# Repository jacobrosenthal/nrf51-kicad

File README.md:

Nordic provides reference designs for Altium only:
https://www.nordicsemi.com/eng/nordic/download_resource/20348/9/5180704

This is the qfac-dcdc from 2.4

Ideally you could use altium's free www.circuitmaker.com to view the paid Circuit Designer files, but thats not the case unless they have already previously been exported as an autocad file:
https://www.youtube.com/watch?v=YAWBsShCId4

As thats not the case for these Nordic files I decided to play.

In the end I finally found a 'free' viewer (for 6 months) from Altium that is really all you need to get a look at the design decisions.
http://www.altium.com/altium-designer-viewer 

However I wanted to play with kicad and https://github.com/thesourcerer8/altium2kicad to see how close it gets

Fixed issues:
* Schematic wouldnt come over for some reason, I had to build that by hand.
* The Polygons didn't come in quite right, I made them Thermal Releif's and Polygons and that seemed to help.
* I dont think you can bring in bare pads, so the antenna pad was lost on import and its signal trace was downsized. 
* Keepout Polys were lost and recreated by hand
* Stiching Vias are.. problematic, in kicad so those needed to be handled by hand https://forum.kicad.info/t/protip-nicer-via-stitching/1103/32
* via drill conversion was wierd, though Im not familar enough with kicad right now to know if it mattered, I hand edited all those a bunch
* File-Archive Footprints->Create library Exported the footprints out of the design into a proper library, and moved the .3dshapes locally as well

Known issues:
* Keepouts are really picky in kicad and Im so far too lazy to stich around all the pads, so traces in that region are showing as airwires even though theyre connected
* Altium has the no poly islands smaller than xsq but kicad doesnt appear to which means a few little islands exist on our gerbers that dont on theirs.

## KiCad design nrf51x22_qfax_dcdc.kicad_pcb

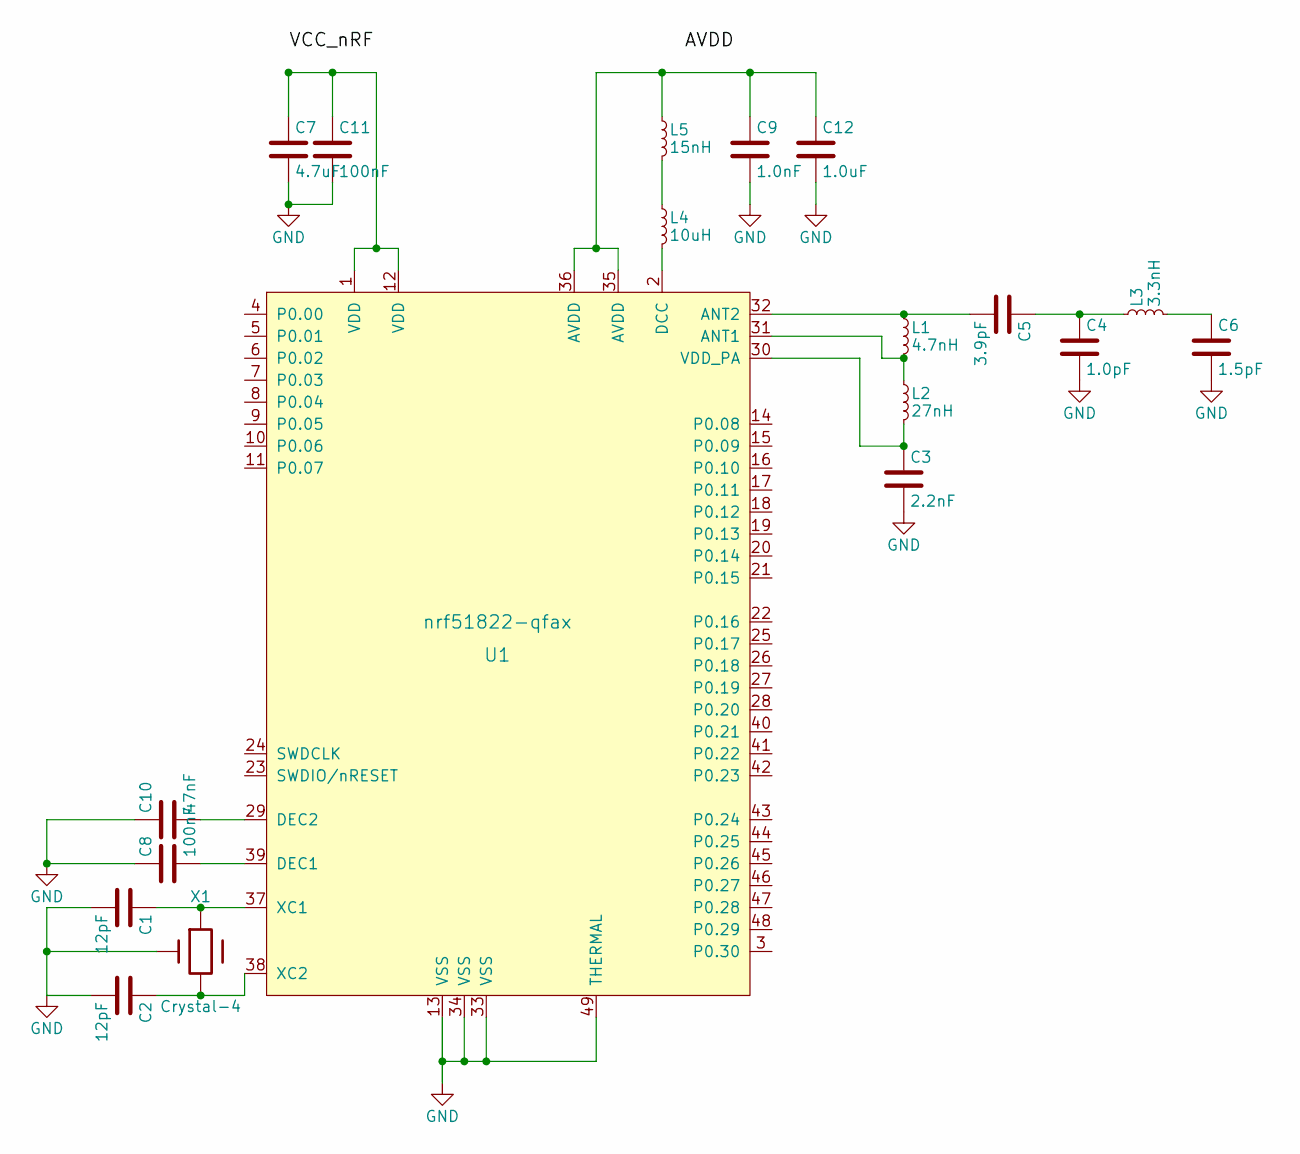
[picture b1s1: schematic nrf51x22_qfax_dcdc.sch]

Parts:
C1, C2: 12pF; CAPC1005X04L
C3: 2.2nF; CAPC1005X04L
C4: 1.0pF; CAPC1005X04L
C5: 3.9pF; CAPC1005X04L
C6: 1.5pF; CAPC1005X04L
C7: 4.7uF; CAPC1608X06L
C8, C11: 100nF; CAPC1005X04L
C9: 1.0nF; CAPC1005X04L
C10: 47nF; CAPC1005X04L
C12: 1.0uF; CAPC1608X06L
L1: 4.7nH; INDC1005X04L
L2: 27nH; INDC1005X04L
L3: 3.3nH; INDC1005X04L
L4: 10uH; INDC1608X06L
L5: 15nH; INDC1005X04L
U1: nrf51822-qfax; nrf51-qfax-1ep-vias
X1: Crystal-4; BT-XTAL_2520

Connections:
GND: C1.2, C2.2, C3.2, C4.2, C6.2, C7.2, C8.1, C9.2, C10.1, C11.2, C12.2, U1.13 (VSS), U1.33 (VSS), U1.34 (VSS), U1.49 (THERMAL), X1.2 (4), X1.4; also elsewhere on the board
unnamed: C1.1, U1.37 (XC1), X1.3
unnamed: C2.1, U1.38 (XC2), X1.1
unnamed: C3.1, L2.2, U1.30 (VDD_PA)
unnamed: C4.1, C5.1, L3.1
unnamed: C5.2, L1.1, U1.32 (ANT2)
unnamed: C6.1, L3.2
unnamed: C8.2, U1.39 (DEC1)
unnamed: C10.2, U1.29 (DEC2)
unnamed: C7.1, C11.1, U1.1 (VDD), U1.12 (VDD)
unnamed: C9.1, C12.1, L5.1, U1.35 (AVDD), U1.36 (AVDD)
unnamed: L1.2, L2.1, U1.31 (ANT1)
unnamed: L4.1, L5.2
unnamed: L4.2, U1.2 (DCC)

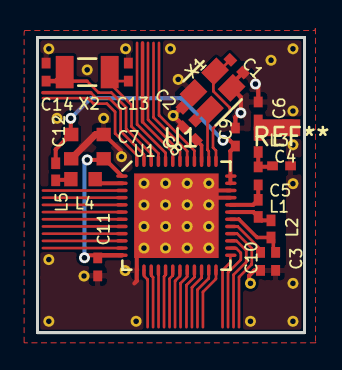
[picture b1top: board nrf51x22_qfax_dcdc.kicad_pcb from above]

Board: 2 copper layers, 14.8 x 16.4 mm, 22 parts (0 on the bottom side), 16 nets.

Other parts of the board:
C13, C14: Chip Capacitor, 2-Leads, Body 1.0x0.5mm, IPC High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; CAPC1005X04L
X2: XTAL SMD 3.2 x 1.5 mm; XTAL_3215

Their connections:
GND: C13.1, C14.1; also elsewhere on the board
XL1: C14.2, X2.2
XL2: C13.2, X2.1

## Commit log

2015-12-12 fresh export of dcdc
2015-12-15 add schematic, symbols, export footprints, clean up
2015-12-15 name change
2015-12-15 README
2015-12-15 missed replacing a via
2015-12-24 refer to local copies of footprint libraries
2015-12-25 library update
2015-12-25 utilize gitignore
2015-12-25 add vias to footprint and swap in
2016-02-27 libraries update
2016-02-27 fix crystal component so hooks grounds to GND, gerbers
2016-02-27 fix missing low freq crystal on schematic
2016-02-27 fill in component fields for bom
2016-03-16 nrf51822 library updates
2016-03-17 update library
